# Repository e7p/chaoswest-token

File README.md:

## Welcome

This is the official documentation of the Chaos-West Token which is given to anyone on the SHA2017 camp and also on the 35C3 who supports us with a reasonable donation for us (mainly to be able to split-up costs we all belonging to Chaos-West share on the event). If you really want to have one of these wonderful and token kits, just come to our Chaos-West info desk on the event and support us with a recommended donation. In case there are some left-overs after the event, it should be somehow possible to receive these if you still want to get a token after the event. The easiest would probably be to write an e-mail to cwtkn@devtal.de which should address the makers of this token. As this is a project released to the public domain, consolidating the thought of open hardware and free software, you can also produce the board by yourself (or wire up the rather simple circuit on a breadboard), but getting it from us really supports the collective activities of Chaos-West, just consider that.

## Quick Start

On 35C3: Please come to me for help flashing!

Elsewise: type `make usbflash` to flash the token.

Attention: When powering the badge it will take about 6 seconds to boot, before anything will be shown (because of the USB firmware upgrade option).

## Package Contents

The token package should consist out of the following components. If something is missing, ask at the Chaos-West main tent for token support.

1. One Printed Circuit Board (PCB)
2. One Coin Cell Holder
3. One Effect-LED (probably you can choose between different ones)
4. One Power Switch
5. Non-Rechargable CR2032 Coin Cell (3 V)
6. Printed Getting Started Guide

If you want to extend your token with additional parts, you can buy all of the neccessary parts afterwards, refer to the part list below for order numbers given as a reference.
You could also ask me for the full version and I could support you with that, as I may have some left-overs from the SHA2017.

## Getting Started

**Warning**: There is no reverse-polarity protection, so be cautionous to insert the battery in the correct direction, the plus-sign of the battery always facing towards you when looking at the side of the PCB with the coin cell holder! If the battery is inserted in the wrong way, it probably will damage other parts of the circuit including the Front LED.

You should have received your token with an [quick start guide](docs/infocard_revb.pdf). Follow the steps and you will get a basic functioning token which blinks when a coin cell is inserted and the switch is slide to the “On”-position. The steps of the printed getting started guide are noted here:

1. Solder the switch.
2. Solder the Coin-Cell holder. The slot should face the top.
3. Solder the Effect LED, mind the polarity (marked “+”) matches with your LED.
4. Insert the battery, switch on, and enjoy the blinking / fading LED effects.

That's it basically. If you want more, read on, as there are many more possibilities in this little token PCB.

## Features

* Front LED lighting up
* Coin Cell Holder for CR2032 (standard) or LIR2032 (Li-Ion) Type Batteries
* Power Switch
* 8-bit Microcontroller with ISP-interface
* (Actually Precise) Temperature Sensor
* Up to Five WS2813 LEDs (and pads for extending to other WS281x-stripes, supporting the new WS2813 ones aswell)
* USB
* Li-Ion Charging Circuit (via USB)
* Microcontroller Firmware In-System-Programmable (ISP) or Directly Via USB

## Partlist

All parts, except from the thru-hole LED on the front are SMD-components, which means that their pins are soldered directly on the exposed pads of the PCB. Some of the components (Diodes, LEDs and ICs) need to be mounted in a specific direction. This direction can be seen on the drawing above. The mount-direction of the six-pin transistor Q1 is not important as the pinout is symmetric. Not all components are essential. Each build step below references the neccessary and optional parts for each step.

Part         | Value           | Description                                           | Farnell
------------ | --------------- | ----------------------------------------------------- | -------
BAT1         | Keystone 3002   | CR2032 / LIR2032 Coin Cell Holder (only use rechargable LIR2032 with Li-Ion Charger, never use CR2032)                     | 1650693
C1,2,5       | 10 nF           | 0805 Ceramic Capacitor (10V)                          | 1759246
C3,4         | 4.7 µF          | 0805 Ceramic Capacitor (10V)                          | 1759427
C6           | 100 nF          | 0805 Ceramic Capacitor (10V)                          | 9406387
D1,2         | 3.6 V Zener     | SOD-123 Zener Diode                                   | 2069437
J1           | Molex 47346     | Female Micro-USB Jack                                 | 1568026
J2           | 2,54mm header   | 6-pin ISP Header (2x3 pins)                           | 2505049
L1           | 33 Ohm @ 10MHz  | 0805 Ferrite Bead                                     | 1800367
LED1         | Standard        | Various different LEDs<sup>1</sup>                    | 1581189
LED2,3,4,5,6 | WS2813          | RGB-LED with integrated controller                    | -<sup>2</sup>
Q1           | Si1967DH        | SOT-363 Dual P-Channel MOSFET                         | 2335282
R1,6         | 68 Ohm          | 0805 Chip Resistor                                    | 2447707
R4           | 47 kOhm         | 0805 Chip Resistor                                    | 2447664
R5           | 1 MOhm          | 0805 Chip Resistor                                    | 2447596
R7           | 2.2 kOhm        | 0805 Chip Resistor                                    | 2447623
SJ1,3,4      | -               | either short or current limiting resistor<sup>1</sup> | 2447606
SW1          | AYZ0102AGRLC    | SPDT Switch                                           | 2319971<sup>3</sup>
U1           | MCP7383xT-2ACI  | Single-Cell Li-Ion Charging IC                        | 1332158
U2           | ATtiny85-20SU   | SOIC-8 20 MHz AVR Microcontroller                     | 1972176
U3           | MCP9700AT-E/LT  | SC70-5 Temperature Sensor                             | 1332165

<sup>1</sup>: For LED1 many options are available (including Effect-LEDs and standard one- and multicolor LEDs). This also results in different possible usages of the solder-jumpers SJ1,3 and 4. Check the specific section "Front LED" for this.<br />
<sup>2</sup>: The WS2813 LEDs are not yet commonly available. Check for example TME, eBay or AliExpress for these.
<sup>3</sup>: Revision B got a different switch, so the switch in Revision A was ALPS SSAJ120100 which has Farnell number 2056803.

### Testpads

There are a few additional pads which are meant for additional features not included in the default version of this board. See this short reference as the full description of these and refer to the schematic for reference.

Pads      | Description
--------- | -----------
+B-       | On these pads an Lithium-Polymer single cell could be soldered when not using the coin-cell holder. When not using the Li-Ion Charger circuit, these pads can generally be used to supply about 2.4 to 5 volts to the board.
DO,BO,GND | These are located beneath LED6 (DO outermost, following BO, and GND most to the center of the board) and are for chaining additional WS281x-LEDs to the board. BO is only used for WS2813 whereas DO is the standard WS281x-signal output of the last on-board WS2813-LED LED6.

## Build

The full feature-set of the token can be only achieved when soldering extensions and doing very small modifications to the board. This section gives an overview about which modification “checkpoints” can be reached at which each more and more features are achieved, yet ranging from very simple one-part soldering jobs up to own modifications on a microcontroller firmware involving even USB-development.

### Essentials

Components: BAT1, LED1, SW1

When receiving your token, you will find an Effect LED, a switch, and coin cell holder within your kit. This is enough to start with a very simple circuit: The LED is connected directly to the battery terminals and thus is lit whenever a coin cell with a sufficiently high voltage is inserted and the switch is turned on.

Any other part of the circuit (like the microcontroller, or a current limiting resistor for the LED) is by default bypassed, which means that some of the pads of the LED solder jumper (SJ1) and the switch (SW1) are interconnected with small traces. If for example the effect LED is exchanged with a standard non-blinking LED, a current limiting resistor is necessary, which means that a small trace between two of the pads of SJ1 must be cut and a sufficiently large-valued (e.g. 220 ohms) resistor soldered there instead.

### Other LED

Components: SJ3, SJ4

Similar to the main LED (see above), SJ3 and SJ4 allow at least two more arbitrary LEDs to be soldered on the front side of the board. Usually the SJ-pads will be connected to the cathode of the LEDs except for one case: common cathode multi-color LEDs. But this will be topic of a following section. This means, that the anode of the LEDs should be connected to one of the 3-5 V (VCC) pads and the cathode (preferably) to the middle pads of SJ1,3,4 which are with vias in the logo brought to the front side. The same as for the main LED has taken into account here: If the LED is blinking, it usually doesn't require a current limiting resistor. If it is a standard (maybe multicolor or RGB) LED, then a current limiting resistor is strictly required, missing resistors causing damage to the LED.

### Li-Ion Charger and USB Jack

TODO

The power switch is also by default bypassed for the charging functionality, which makes it necessary to cut traces connected with the switches pads. The switch has three pins of which two are by default connected together. For using the Li-Ion Charging circuit, you need to cut the trace for this step. The trace to be cut is marked with a very small black box of silk screen.

Never use the charging circuit for normal CR2032 coin cells. If you solder, you can only use single Li-Ion Cells in the coin cell holder or on the exposed battery pads (for larger battery packs).

R4: for greater Li-Ion Cells can be other (330mAh: 4k works), charging-rate originally set for smaller LIR2032 (about 20mAh). Refer to the MCP7383 datasheet for more details on this “Program” resistor.

R7: This from the schematic is connected between USB-DM and +5V, but it must be connected between USB-DM and VCC. Otherwise it _won't boot_ when a bootloader is flashed on the Microcontroller and run from the battery. So it is neccessary to solder only the USB-DM pad of R7 to the resistor and leave the other side of the resistor in the air and then solder some copper wire between this and a VCC pad.

### Microcontroller and ISP Port

TODO

When using the bootloader, keep in mind that R7 needs to be bodge-wired (see topic “Li-Ion Charger and USB Jack”.

### Temperature Sensor

The MCP9700AT-E/LT temperature sensor has an range of -40°C to 125°C with a maximum tolerance of ±2°C tolerance. If it is calibrated at 25°C, a tolerance of ±1°C can be achieved. It is connected to pin PB2 and can be read out using the Analog/Digital-Converter channel 1 (ADC1).

### WS2813 LEDs

There are footprints on the board for up to five WS2813-type LEDs. These integrate a full-color RGB-PWM generator and 24-bit shift register logic which allows to chain this kind of LEDs to a long chain which is controlled by a single pin.

## Front LED

### Options
* Single Color (red, amber, yellow, green, blue, pink, white, UV, IR) Standard LED
* Common-Anode RGB-LED
* Common-Cathode RGB-LED
* Disco Effect LED
* Slow-Fading Effect LED
* Blinking LED
* [WS2812 Thru-Hole LED](https://www.adafruit.com/product/1938)
* ... possibly any 10/5/3mm Thru-Hole LED one could think of

In any case, the status of the LED can be controlled by the microcontroller, if it is fitted and the solder jumpers are set correctly.

## USB

The USB jack can be used to charge the Li-Ion battery or to exchange data between an USB-host and the microcontroller on the token. With a special bootloader, it is also possible to flash the microcontroller firmware directly over the USB-port, so there is really nothing more than a standard USB-port on a PC needed to start developing own programs and flashing them to the token. An ISP-type-programmer is then only necessary for programming the bootloader into the microcontroller for the very first time.

### Bootloader
[micronucleus](https://github.com/micronucleus/micronucleus)

To write the Bootloader, connect via ISP port (or SO-8 clamp directly on the AtTiny).

_Important_: It is neccessary to flash without the temperature sensor, as it would override the clock pin of the ISP process.

Flash the Bootloader (micronucleus default build for ATTiny85 or Digispark) with the following commands:

1. `cd firmware`
2. `make flash fuse` (only continue if successfully and connectable via USB; DigiSpark Driver)
3. `make disablereset` (this _disables_ the Reset functionality and won't allow you to flash the ATTiny85 again via ISP. After this fusing it is only possible via HVSP to rescue a wrongly flashed ATTiny85).

When using the bootloader, keep in mind that R7 needs to be bodge-wired (see topic “Li-Ion Charger and USB Jack”.

## Firmware

`make usbflash` should be enough to flash to a token with installed micronucleus bootloader.

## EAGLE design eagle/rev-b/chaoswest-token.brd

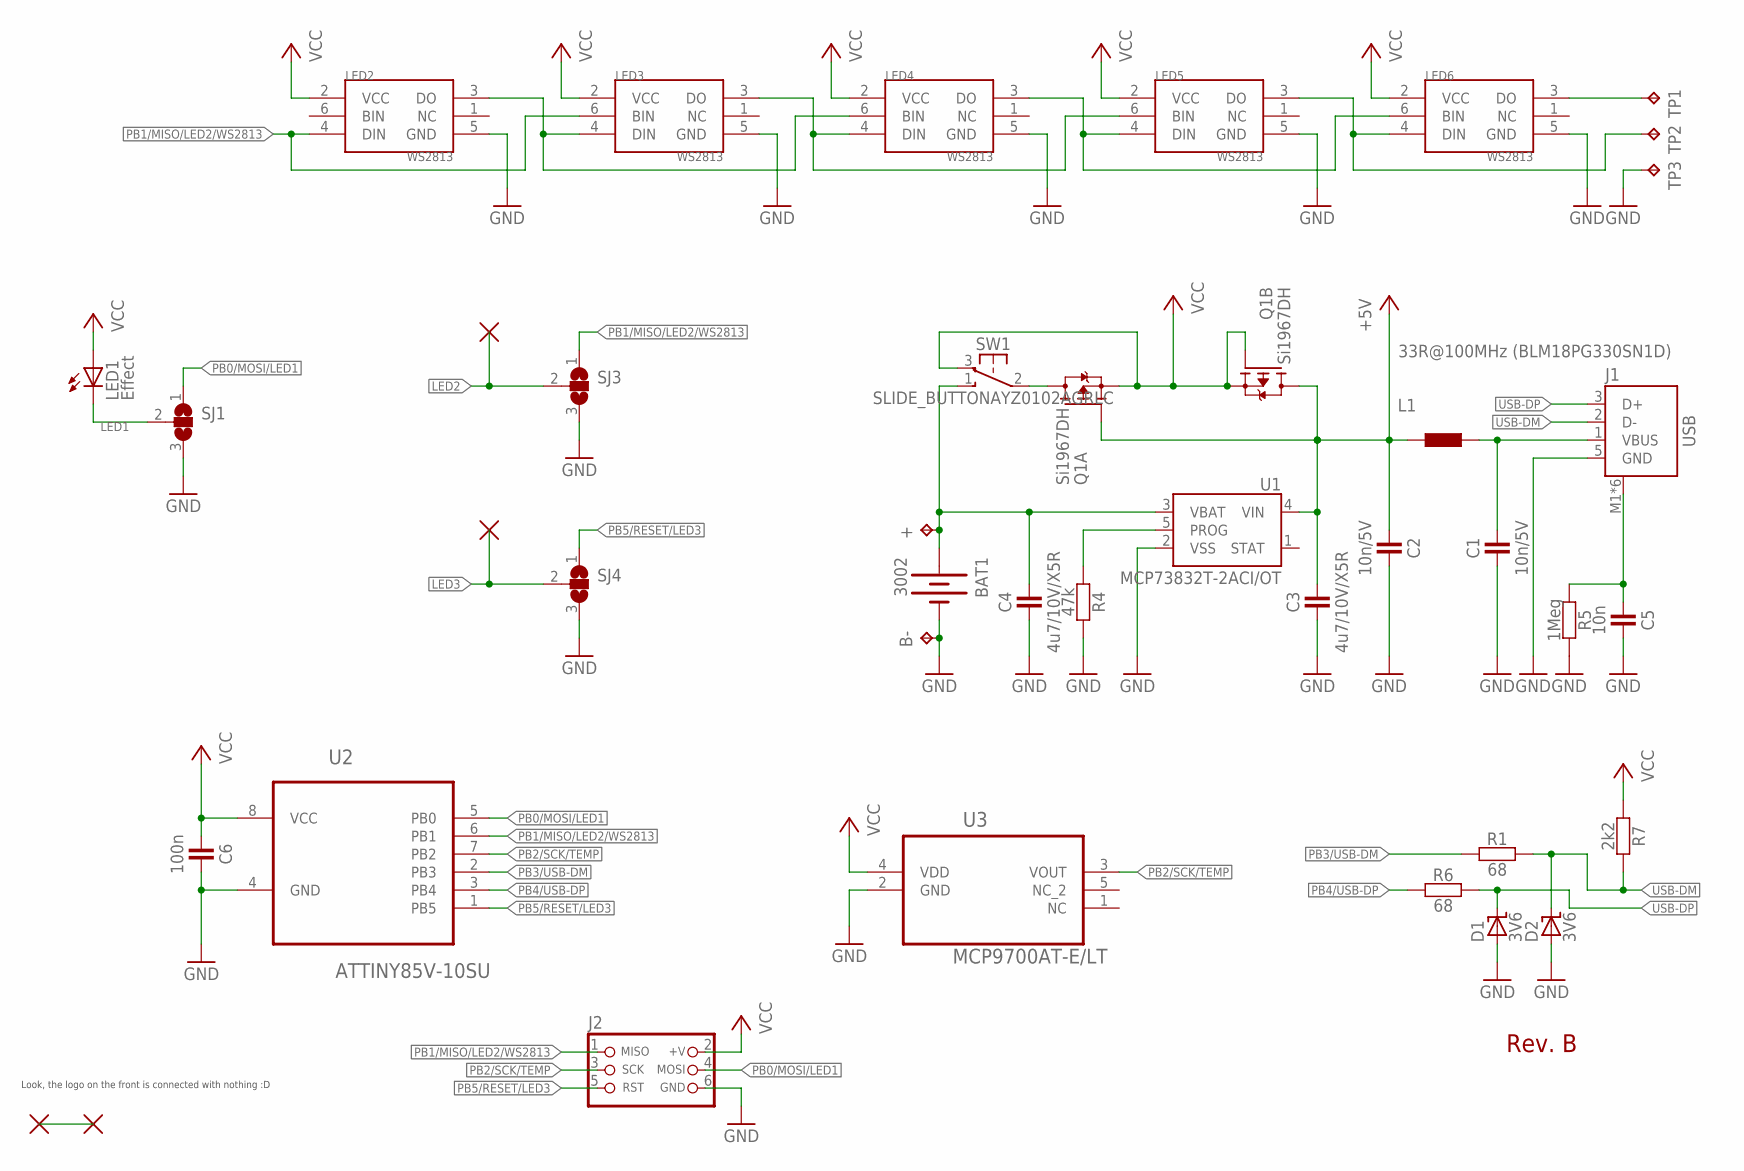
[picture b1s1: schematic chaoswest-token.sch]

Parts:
+: TPTP18SQ; TP18SQ
B-: TPTP18SQ; TP18SQ
BAT1: 3002; BATTCON_20MM
C1, C2: 10n/5V; C0805
C3, C4: 4u7/10V/X5R; C0805
C5: 10n; C0805
C6: 100n; C0805
D1, D2: 3V6; SOD123
J1: USB; MOLEX_47346-0001
J2: ISP; M2X3_SMD
L1: 33R@100MHz (BLM18PG330SN1D); C0805
LED1: Effect; LED5MM
LED2, LED3, LED4, LED5, LED6: WS2813
Q1: Si1967DH; SOT363
R1, R6: 68; C0805
R4: 47k; C0805
R5: 1Meg; C0805
R7: 2k2; C0805
SJ1, SJ3, SJ4: SJ2W; SJ_2
SW1: SLIDE_BUTTONAYZ0102AGRLC; AYZ0102AGRLC
TP1: DO; TP09SQ
TP2: BO; TP09SQ
TP3: GND; TP09SQ
U1: MCP73832T-2ACI/OT; SOT23-5
U2: ATTINY85V-10SU; SOIC127P798X216-8N
U3: MCP9700AT-E/LT; SOT65P210X110-5N
U$1, U$2, U$3, U$4: EMPTY_SIGNAL; SMALLSPOT

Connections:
+5V: C2.1, C3.1, L1.2, Q1.2 (G), Q1.3 (D), U1.4 (VIN)
GND: B-.TP, BAT1.-, C1.2, C2.2, C3.2, C4.2, C5.2, C6.2, D1.A, D2.A, J1.5 (GND), J2.6 (GND), LED2.5 (GND), LED3.5 (GND), LED4.5 (GND), LED5.5 (GND), LED6.5 (GND), R4.1, R5.1, SJ1.3, SJ3.3, SJ4.3, TP3.TP, U1.2 (VSS), U2.4 (GND), U3.2 (GND)
LED1: LED1.K (C), SJ1.2
LED2: SJ3.2, U$3.X
LED3: SJ4.2, U$4.X
unnamed: LED2.3 (DO), LED3.4 (DIN), LED4.6 (BIN)
unnamed: Q1.6 (D), SW1.2 (P1)
unnamed: LED3.3 (DO), LED4.4 (DIN), LED5.6 (BIN)
unnamed: U$1.X, U$2.X
unnamed: R4.2, U1.5 (PROG)
unnamed: LED4.3 (DO), LED5.4 (DIN), LED6.6 (BIN)
unnamed: LED5.3 (DO), LED6.4 (DIN), TP2.TP
unnamed: LED6.3 (DO), TP1.TP
unnamed: C5.1, J1.M1 (SHIELD), J1.M2 (SHIELD), J1.M3 (SHIELD), J1.M4 (SHIELD), J1.M5 (SHIELD), J1.M6 (SHIELD), R5.2
PB0/MOSI/LED1: J2.4 (MOSI), SJ1.1, U2.5 (PB0)
PB1/MISO/LED2/WS2813: J2.1 (MISO), LED2.4 (DIN), LED3.6 (BIN), SJ3.1, U2.6 (PB1)
PB2/SCK/TEMP: J2.3 (SCK), U2.7 (PB2), U3.3 (VOUT)
PB3/USB-DM: R1.2, U2.2 (PB3)
PB4/USB-DP: R6.2, U2.3 (PB4)
PB5/RESET/LED3: J2.5 (RST), SJ4.1, U2.1 (PB5)
USB-DM: D2.C, J1.2 (D-), R1.1, R7.1
USB-DP: D1.C, J1.3 (D+), R6.1
VBAT: +.TP, BAT1.+1 (+), BAT1.+2 (+), C4.1, SW1.1 (S1), U1.3 (VBAT)
VBUS: C1.1, J1.1 (VBUS), L1.1
VCC: C6.1, J2.2 (+V), LED1.A, LED2.2 (VCC), LED3.2 (VCC), LED4.2 (VCC), LED5.2 (VCC), LED6.2 (VCC), Q1.1 (S), Q1.4 (S), Q1.5 (G), R7.2, SW1.3 (O1), U2.8 (VCC), U3.4 (VDD)

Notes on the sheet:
Look, the logo on the front is connected with nothing :D
Rev. B

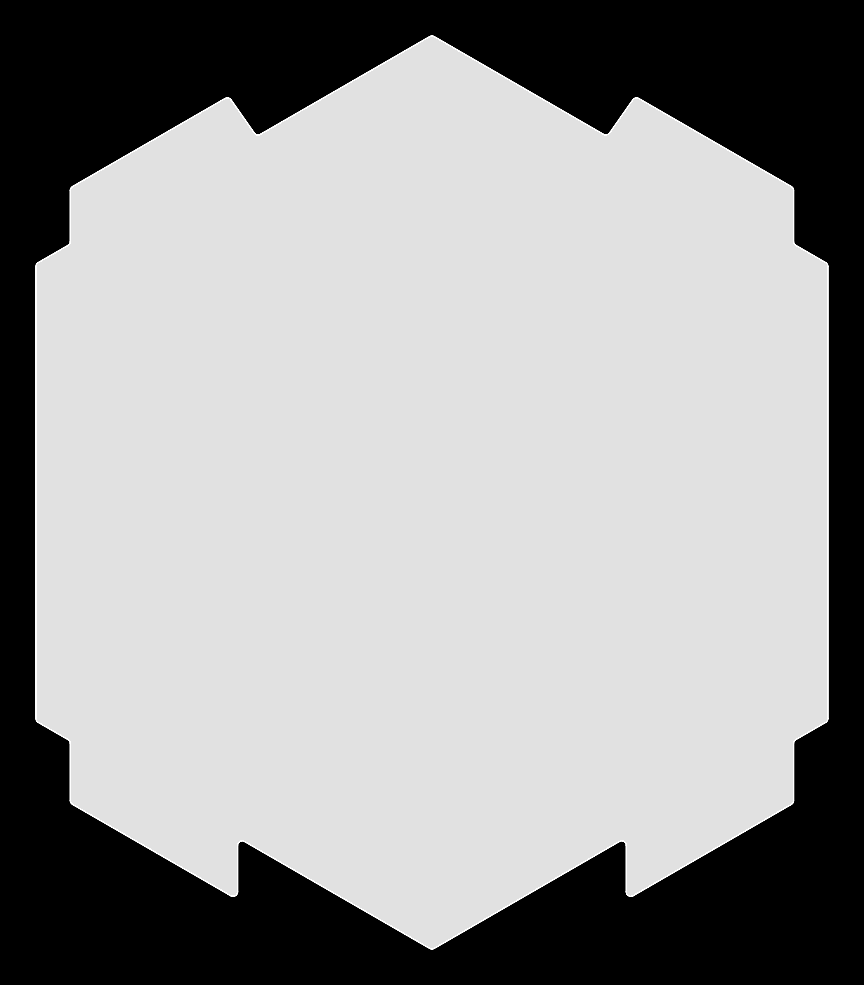
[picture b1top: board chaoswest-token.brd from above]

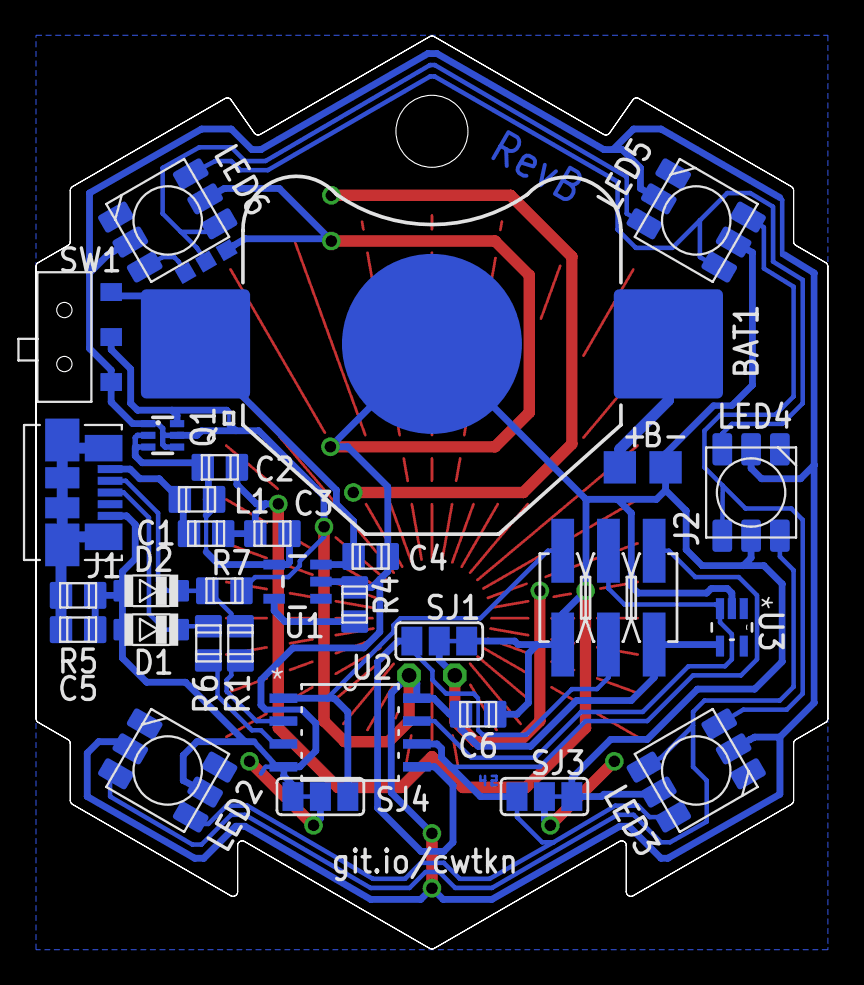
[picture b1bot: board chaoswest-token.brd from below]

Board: 2 copper layers, 44.0 x 50.7 mm, 40 parts (35 on the bottom side), 25 nets.

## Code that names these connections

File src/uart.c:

/*  
 Author: Mark Osborne, BecomingMaker.com
 See accompanying post http://becomingmaker.com/
 
 An example of USI Serial Send for ATtiny25/45/85.
 Sends a text message every second.
   
  ATTiny85 Hookup

  RESET -|1 v 8|- Vcc
    PB3 -|2   7|- PB2/SCK
    PB4 -|3   6|- PB1/MISO/DO
    GND -|4 _ 5|- PB0/MOSI/SDA

ATTiny85 PB1/MISO/DO = Serial UART Tx -> connect to Rx of serial output device
*/

/* Supported combinations:
 *   F_CPU 1000000   BAUDRATE 1200, 2400 
 *   F_CPU 8000000   BAUDRATE 9600, 19200
 *   F_CPU 16000000  BAUDRATE 9600, 19200, 28800, 38400
 */

#include <avr/io.h>
#include <avr/interrupt.h>
#include <stdio.h>

// Set your baud rate and number of stop bits here
#define BAUDRATE            9600
#define STOPBITS            1
//F_CPU defined by Arduino, e.g. 1000000, 8000000, 16000000
//#define F_CPU 8000000

// If bit width in cpu cycles is greater than 255 then  divide by 8 to fit in timer
// Calculate prescaler setting
#define CYCLES_PER_BIT       ( (F_CPU) / (BAUDRATE) )
#if (CYCLES_PER_BIT > 255)
#define DIVISOR             8
#define CLOCKSELECT         2
#else
#define DIVISOR             1
#define CLOCKSELECT         1
#endif
#define FULL_BIT_TICKS      ( (CYCLES_PER_BIT) / (DIVISOR) )

// Old timer values
#ifdef ARDUINO
volatile static uint8_t oldTCCR0A;
volatile static uint8_t oldTCCR0B;
volatile static uint8_t oldTCNT0;
#endif

// USISerial send state variable and accessors
enum USISERIAL_SEND_STATE { AVAILABLE, FIRST, SECOND };
static volatile enum USISERIAL_SEND_STATE usiserial_send_state = AVAILABLE;
static inline enum USISERIAL_SEND_STATE usiserial_send_get_state(void)
{
    return usiserial_send_state;
}
static inline void usiserial_send_set_state(enum USISERIAL_SEND_STATE state)
{
    usiserial_send_state=state;
}
uint8_t usiserial_send_available()
{
    return usiserial_send_get_state()==AVAILABLE;
}

// Transmit data persistent between USI OVF interrupts
static volatile uint8_t usiserial_tx_data;
static inline uint8_t usiserial_get_tx_data(void)
{
    return usiserial_tx_data;
}
static inline void usiserial_set_tx_data(uint8_t tx_data)
{
    usiserial_tx_data = tx_data;
}

static uint8_t reverse_byte (uint8_t x) {
    x = ((x >> 1) & 0x55) | ((x << 1) & 0xaa);
    x = ((x >> 2) & 0x33) | ((x << 2) & 0xcc);
    x = ((x >> 4) & 0x0f) | ((x << 4) & 0xf0);
    return x;
}

void usiserial_send_byte(uint8_t data)
{
    while (usiserial_send_get_state() != AVAILABLE)
    {
        // Spin until we finish sending previous packet
    };
    usiserial_send_set_state(FIRST);
    usiserial_set_tx_data(reverse_byte(data));

    // Save current Arduino timer state
#ifdef ARDUINO    
    oldTCCR0B = TCCR0B;
    oldTCCR0A = TCCR0A;
    oldTCNT0 = TCNT0;
#endif
 
    // Configure Timer0
    TCCR0A = 2<<WGM00;                      // CTC mode
    TCCR0B = CLOCKSELECT;                   // Set prescaler to clk or clk /8
    GTCCR |= 1 << PSR0;                     // Reset prescaler
    OCR0A = FULL_BIT_TICKS;                 // Trigger every full bit width
    TCNT0 = 0;                              // Count up from 0 

    // Configure USI to send high start bit and 7 bits of data
    USIDR = 0x00 |                            // Start bit (low)
        usiserial_get_tx_data() >> 1;         // followed by first 7 bits of serial data
    USICR  = (1<<USIOIE)|                     // Enable USI Counter OVF interrupt.
        (0<<USIWM1)|(1<<USIWM0)|              // Select three wire mode to ensure USI written to PB1
        (0<<USICS1)|(1<<USICS0)|(0<<USICLK);  // Select Timer0 Compare match as USI Clock source.
    DDRB  |= (1<<PB1);                        // Configure USI_DO as output.
    USISR = 1<<USIOIF |                       // Clear USI overflow interrupt flag
        (16 - 8);                             // and set USI counter to count 8 bits
}

// USI overflow interrupt indicates we have sent a buffer
ISR (USI_OVF_vect) {
    if (usiserial_send_get_state() == FIRST)
    {
        usiserial_send_set_state(SECOND);
        USIDR = usiserial_get_tx_data() << 7  // Send last 1 bit of data
            | 0x7F;                           // and stop bits (high)
        USISR = 1<<USIOIF |                   // Clear USI overflow interrupt flag
            (16 - (1 + (STOPBITS)));          // Set USI counter to send last data bit and stop bits
    }
    else
    {
        PORTB |= 1 << PB1;                    // Ensure output is high
        DDRB  |= (1<<PB1);                    // Configure USI_DO as output.
        USICR = 0;                            // Disable USI.
        USISR |= 1<<USIOIF;                   // clear interrupt flag

        //Restore old timer values for Arduino
#ifdef ARDUINO
        TCCR0A = oldTCCR0A;
        TCCR0B = oldTCCR0B;
        // Note Arduino millis() and micros() will lose the time it took us to send a byte
        // Approximately 1ms at 9600 baud
        TCNT0 = oldTCNT0;
#endif

        usiserial_send_set_state(AVAILABLE);
    }
}

int printCHAR(char character, FILE *stream)
{
	usiserial_send_byte(character);

	return 0;
}

FILE uart_str = FDEV_SETUP_STREAM(printCHAR, NULL, _FDEV_SETUP_RW);

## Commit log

2017-06-23 initial commit, adding current eagle state and also the design track and some readme
2017-06-24 current status of board (front side quasi final) and some more dxf / xml files added
2017-06-24 current front view from eagle added
2017-06-24 current inventor file added
2017-06-25 schematic should be mostly done, routing is in process, 42 airwires left
2017-06-26 routing finished, single layer layout
2017-06-26 schematic added as PDF
2017-06-26 minor change at the default jumper settings of the switch
2017-06-26 put the bottom silk screen (component names) into place
2017-06-28 current (hopefully nearly final) state of the PCB, minor changes, gerber files produced
2017-06-28 outlines added to gerbers
2017-06-30 production zip added
2017-07-02 eagle showcase added as PNG
2017-07-26 documentation updated to the current state
2017-08-02 first code (not clean!) push
2017-08-04 Firmware added (test)
2017-08-04 first animation added
2017-08-04 readme
2017-08-08 current firmware status, WS2813 for some reason non working
2017-08-08 sha documentation prints added
2017-08-16 readme important documentations
2018-10-31 pcb revision b added for new production cycle
2018-11-14 Rev B Hardware completed and ordered
2018-12-27 documentation modified to match for Rev B
2018-12-27 documentation image modified
